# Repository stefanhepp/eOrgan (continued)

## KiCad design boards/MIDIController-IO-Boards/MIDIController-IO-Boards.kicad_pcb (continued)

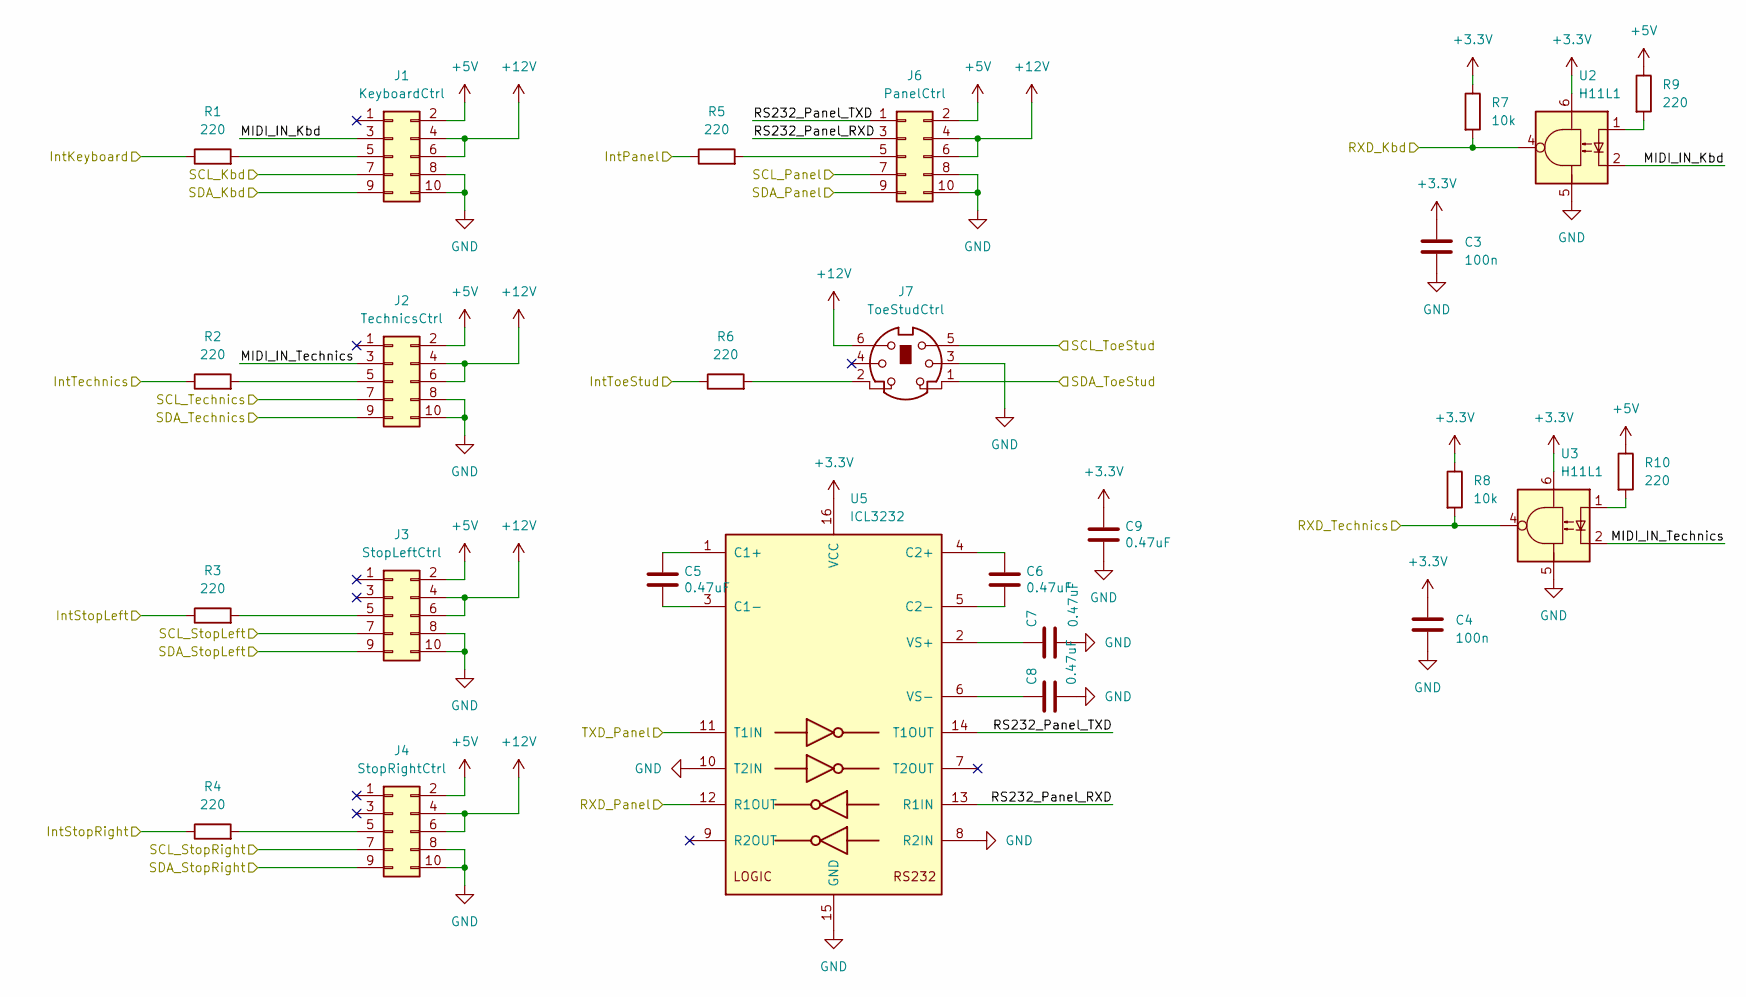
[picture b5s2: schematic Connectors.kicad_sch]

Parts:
C3, C4: 100n; C_Disc_D5.0mm_W2.5mm_P5.00mm
C5, C6, C7, C8, C9: 0.47uF; C_Rect_L7.0mm_W3.5mm_P5.00mm; Voltage 50V
J1: KeyboardCtrl; IDC-Header_2x05_P2.54mm_Horizontal
J2: TechnicsCtrl; IDC-Header_2x05_P2.54mm_Horizontal
J3: StopLeftCtrl; IDC-Header_2x05_P2.54mm_Horizontal
J4: StopRightCtrl; IDC-Header_2x05_P2.54mm_Horizontal
J6: PanelCtrl; IDC-Header_2x05_P2.54mm_Horizontal
J7: ToeStudCtrl; MiniDIN TE_5749180-1
R1, R2, R3, R4, R5, R6, R9, R10: 220; R_Axial_DIN0207_L6.3mm_D2.5mm_P10.16mm_Horizontal
R7, R8: 10k; R_Axial_DIN0207_L6.3mm_D2.5mm_P10.16mm_Horizontal
U2, U3: H11L1; DIP-6_W7.62mm
U5: ICL3232; DIP-16_W7.62mm

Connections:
+3.3V: C3.1, C4.1, C9.1, R7.1, R8.1, U2.6, U3.6, U5.16 (VCC); also elsewhere on the board
+5V: J1.2, J2.2, J3.2, J4.2, J6.2, R9.1, R10.1; also elsewhere on the board
+12V: J1.4, J1.6, J2.4, J2.6, J3.4, J3.6, J4.4, J4.6, J6.4, J6.6, J7.6; also elsewhere on the board
/Connectors/MIDI_IN_Kbd: J1.3, U2.2
/Connectors/MIDI_IN_Technics: J2.3, U3.2
/Connectors/RS232_Panel_RXD: J6.3, U5.13 (R1IN)
/Connectors/RS232_Panel_TXD: J6.1, U5.14 (T1OUT)
/IntKeyboard: R1.1; also elsewhere on the board
/IntPanel: R5.1; also elsewhere on the board
/IntStopLeft: R3.1; also elsewhere on the board
/IntStopRight: R4.1; also elsewhere on the board
/IntTechnics: R2.1; also elsewhere on the board
/IntToeStud: R6.1; also elsewhere on the board
/RXD_Kbd: R7.2, U2.4; also elsewhere on the board
/RXD_Panel: U5.12 (R1OUT); also elsewhere on the board
/RXD_Technics: R8.2, U3.4; also elsewhere on the board
/SCL_Kbd: J1.7; also elsewhere on the board
/SCL_Panel: J6.7; also elsewhere on the board
/SCL_StopLeft: J3.7; also elsewhere on the board
/SCL_StopRight: J4.7; also elsewhere on the board
/SCL_Technics: J2.7; also elsewhere on the board
/SCL_ToeStud: J7.5; also elsewhere on the board
/SDA_Kbd: J1.9; also elsewhere on the board
/SDA_Panel: J6.9; also elsewhere on the board
/SDA_StopLeft: J3.9; also elsewhere on the board
/SDA_StopRight: J4.9; also elsewhere on the board
/SDA_Technics: J2.9; also elsewhere on the board
/SDA_ToeStud: J7.1; also elsewhere on the board
/TXD_Panel: U5.11 (T1IN); also elsewhere on the board
GND: C3.2, C4.2, C7.2, C8.2, C9.2, J1.8, J1.10, J2.8, J2.10, J3.8, J3.10, J4.8, J4.10, J6.8, J6.10, J7.3, U2.5, U3.5, U5.8 (R2IN), U5.10 (T2IN), U5.15 (GND); also elsewhere on the board
unnamed: J1.5, R1.2
unnamed: J2.5, R2.2
unnamed: J3.5, R3.2
unnamed: J4.5, R4.2
unnamed: J6.5, R5.2
unnamed: J7.2, R6.2
unnamed: R9.2, U2.1
unnamed: R10.2, U3.1
unnamed: C5.1, U5.1 (C1+)
unnamed: C5.2, U5.3 (C1-)
unnamed: C6.1, U5.4 (C2+)
unnamed: C6.2, U5.5 (C2-)
unnamed: C7.1, U5.2 (VS+)
unnamed: C8.1, U5.6 (VS-)

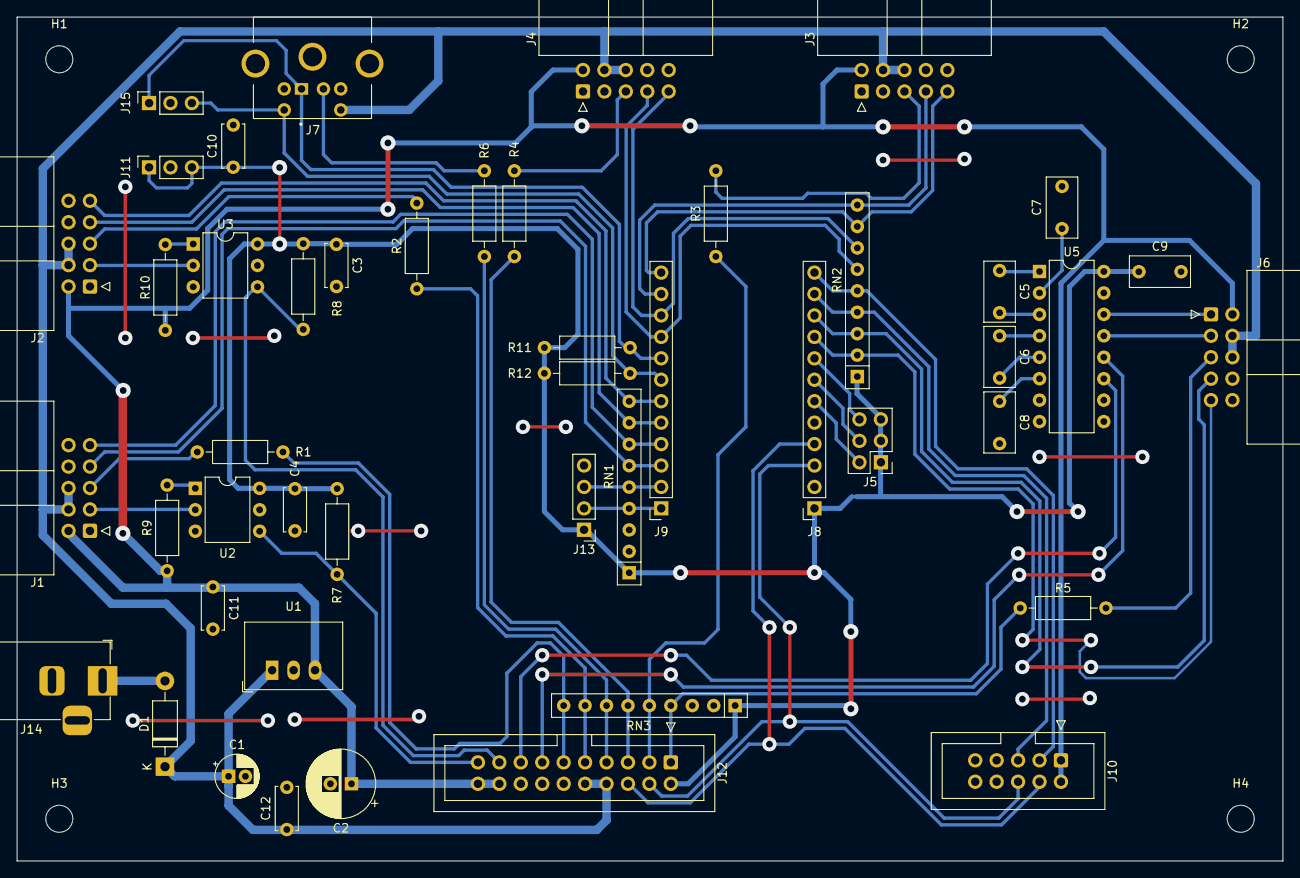
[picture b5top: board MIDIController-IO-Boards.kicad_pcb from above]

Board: 2 copper layers, 150.0 x 100.0 mm, 51 parts (0 on the bottom side), 54 nets.

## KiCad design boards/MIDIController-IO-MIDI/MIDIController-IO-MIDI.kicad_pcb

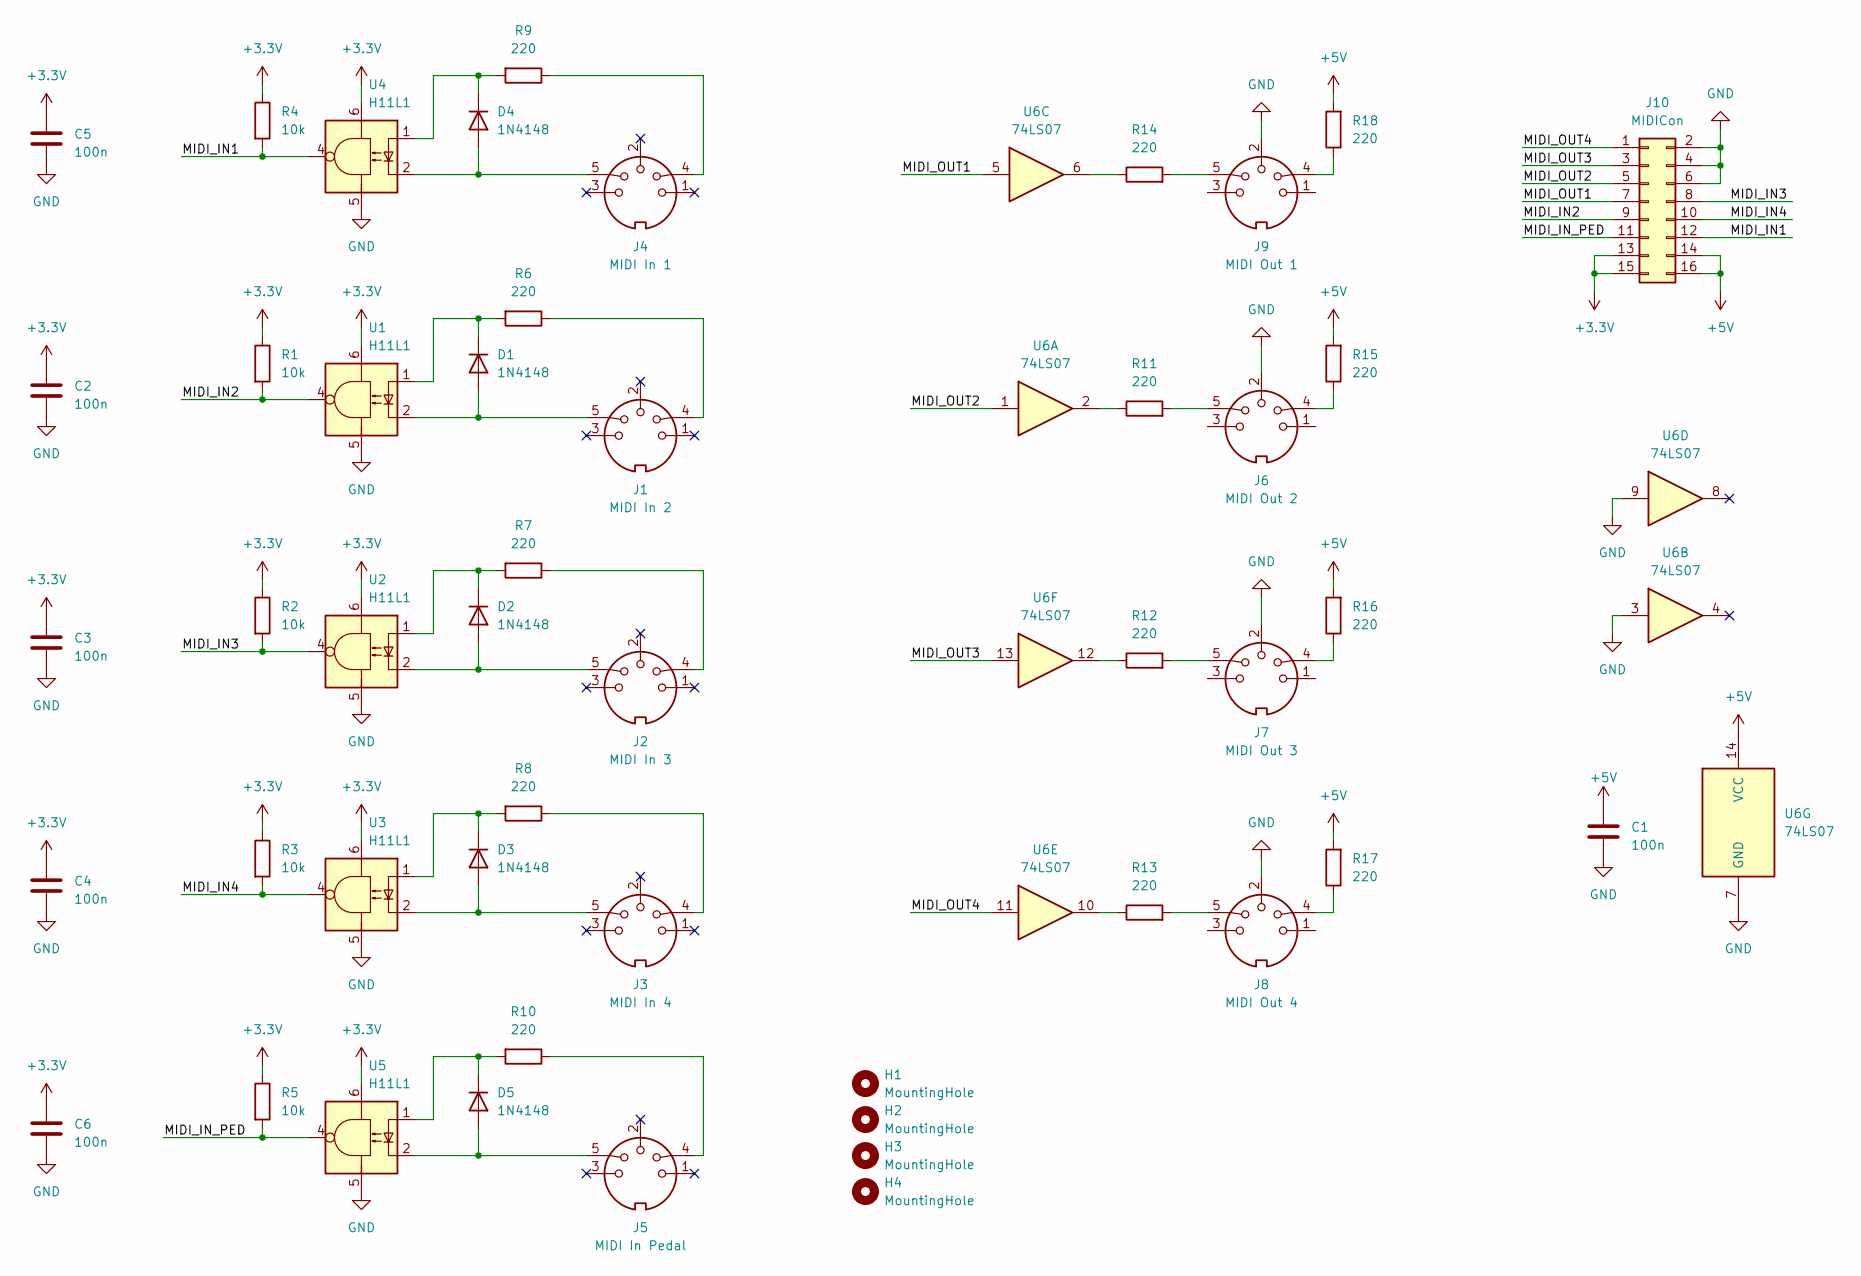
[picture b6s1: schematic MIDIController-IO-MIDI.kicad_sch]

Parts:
C1, C2, C3, C4, C5, C6: 100n; C_Disc_D5.0mm_W2.5mm_P5.00mm
D1, D2, D3, D4, D5: 1N4148; D_DO-35_SOD27_P7.62mm_Horizontal
H1, H2, H3, H4: MountingHole; MountingHole_3.2mm_M3
J1: MIDI In 2; DIN-5 MAB5P
J2: MIDI In 3; DIN-5 MAB5P
J3: MIDI In 4; DIN-5 MAB5P
J4: MIDI In 1; DIN-5 MAB5P
J5: MIDI In Pedal; DIN-5 MAB5P
J6: MIDI Out 2; DIN-5 MAB5P
J7: MIDI Out 3; DIN-5 MAB5P
J8: MIDI Out 4; DIN-5 MAB5P
J9: MIDI Out 1; DIN-5 MAB5P
J10: MIDICon; IDC-Header_2x08_P2.54mm_Vertical
R1, R2, R3, R4, R5: 10k; R_Axial_DIN0207_L6.3mm_D2.5mm_P10.16mm_Horizontal
R6, R7, R8, R9, R10, R11, R12, R13, R14, R15, R16, R17, R18: 220; R_Axial_DIN0207_L6.3mm_D2.5mm_P10.16mm_Horizontal
U1, U2, U3, U4, U5: H11L1; DIP-6_W7.62mm
U6: 74LS07; DIP-14_W7.62mm

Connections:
+3.3V: C2.1, C3.1, C4.1, C5.1, C6.1, J10.13, J10.15, R1.1, R2.1, R3.1, R4.1, R5.1, U1.6, U2.6, U3.6, U4.6, U5.6
+5V: C1.1, J10.14, J10.16, R15.2, R16.2, R17.2, R18.2, U6.14 (VCC)
/MIDI_IN1: J10.12, R4.2, U4.4
/MIDI_IN2: J10.9, R1.2, U1.4
/MIDI_IN3: J10.8, R2.2, U2.4
/MIDI_IN4: J10.10, R3.2, U3.4
/MIDI_IN_PED: J10.11, R5.2, U5.4
/MIDI_OUT1: J10.7, U6.5
/MIDI_OUT2: J10.5, U6.1
/MIDI_OUT3: J10.3, U6.13
/MIDI_OUT4: J10.1, U6.11
GND: C1.2, C2.2, C3.2, C4.2, C5.2, C6.2, J6.2, J7.2, J8.2, J9.2, J10.2, J10.4, J10.6, U1.5, U2.5, U3.5, U4.5, U5.5, U6.3, U6.7 (GND), U6.9
unnamed: D1.2 (A), J1.5, U1.2
unnamed: D1.1 (K), R6.2, U1.1
unnamed: D2.2 (A), J2.5, U2.2
unnamed: D2.1 (K), R7.2, U2.1
unnamed: D3.2 (A), J3.5, U3.2
unnamed: D3.1 (K), R8.2, U3.1
unnamed: D4.2 (A), J4.5, U4.2
unnamed: D4.1 (K), R9.2, U4.1
unnamed: D5.2 (A), J5.5, U5.2
unnamed: D5.1 (K), R10.2, U5.1
unnamed: J1.4, R6.1
unnamed: J2.4, R7.1
unnamed: J3.4, R8.1
unnamed: J4.4, R9.1
unnamed: J5.4, R10.1
unnamed: J6.4, R15.1
unnamed: J6.5, R11.2
unnamed: J7.4, R16.1
unnamed: J7.5, R12.2
unnamed: J8.4, R17.1
unnamed: J8.5, R13.2
unnamed: J9.4, R18.1
unnamed: J9.5, R14.2
unnamed: R11.1, U6.2
unnamed: R12.1, U6.12
unnamed: R13.1, U6.10
unnamed: R14.1, U6.6

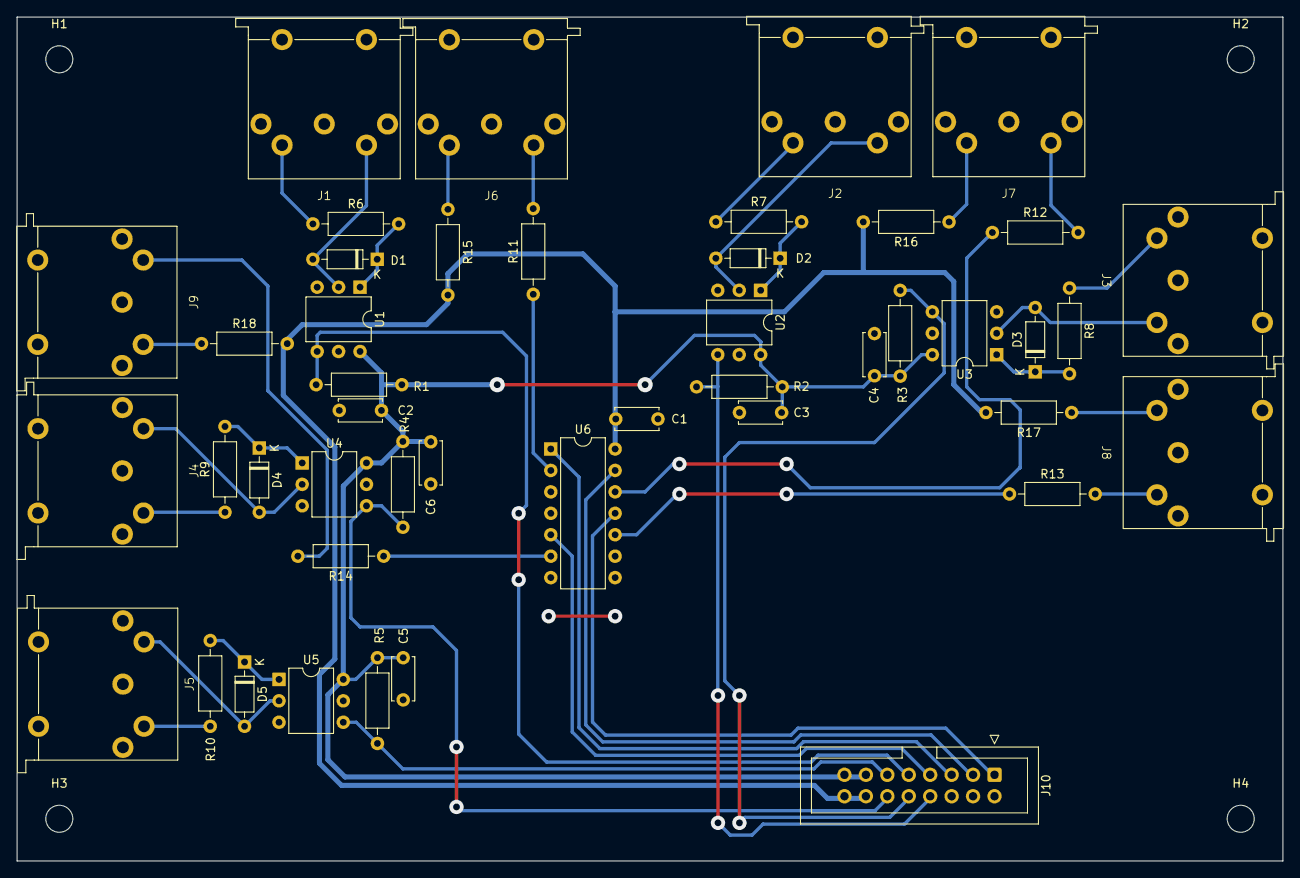
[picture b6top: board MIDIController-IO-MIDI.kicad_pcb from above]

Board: 2 copper layers, 150.0 x 100.0 mm, 49 parts (0 on the bottom side), 39 nets.

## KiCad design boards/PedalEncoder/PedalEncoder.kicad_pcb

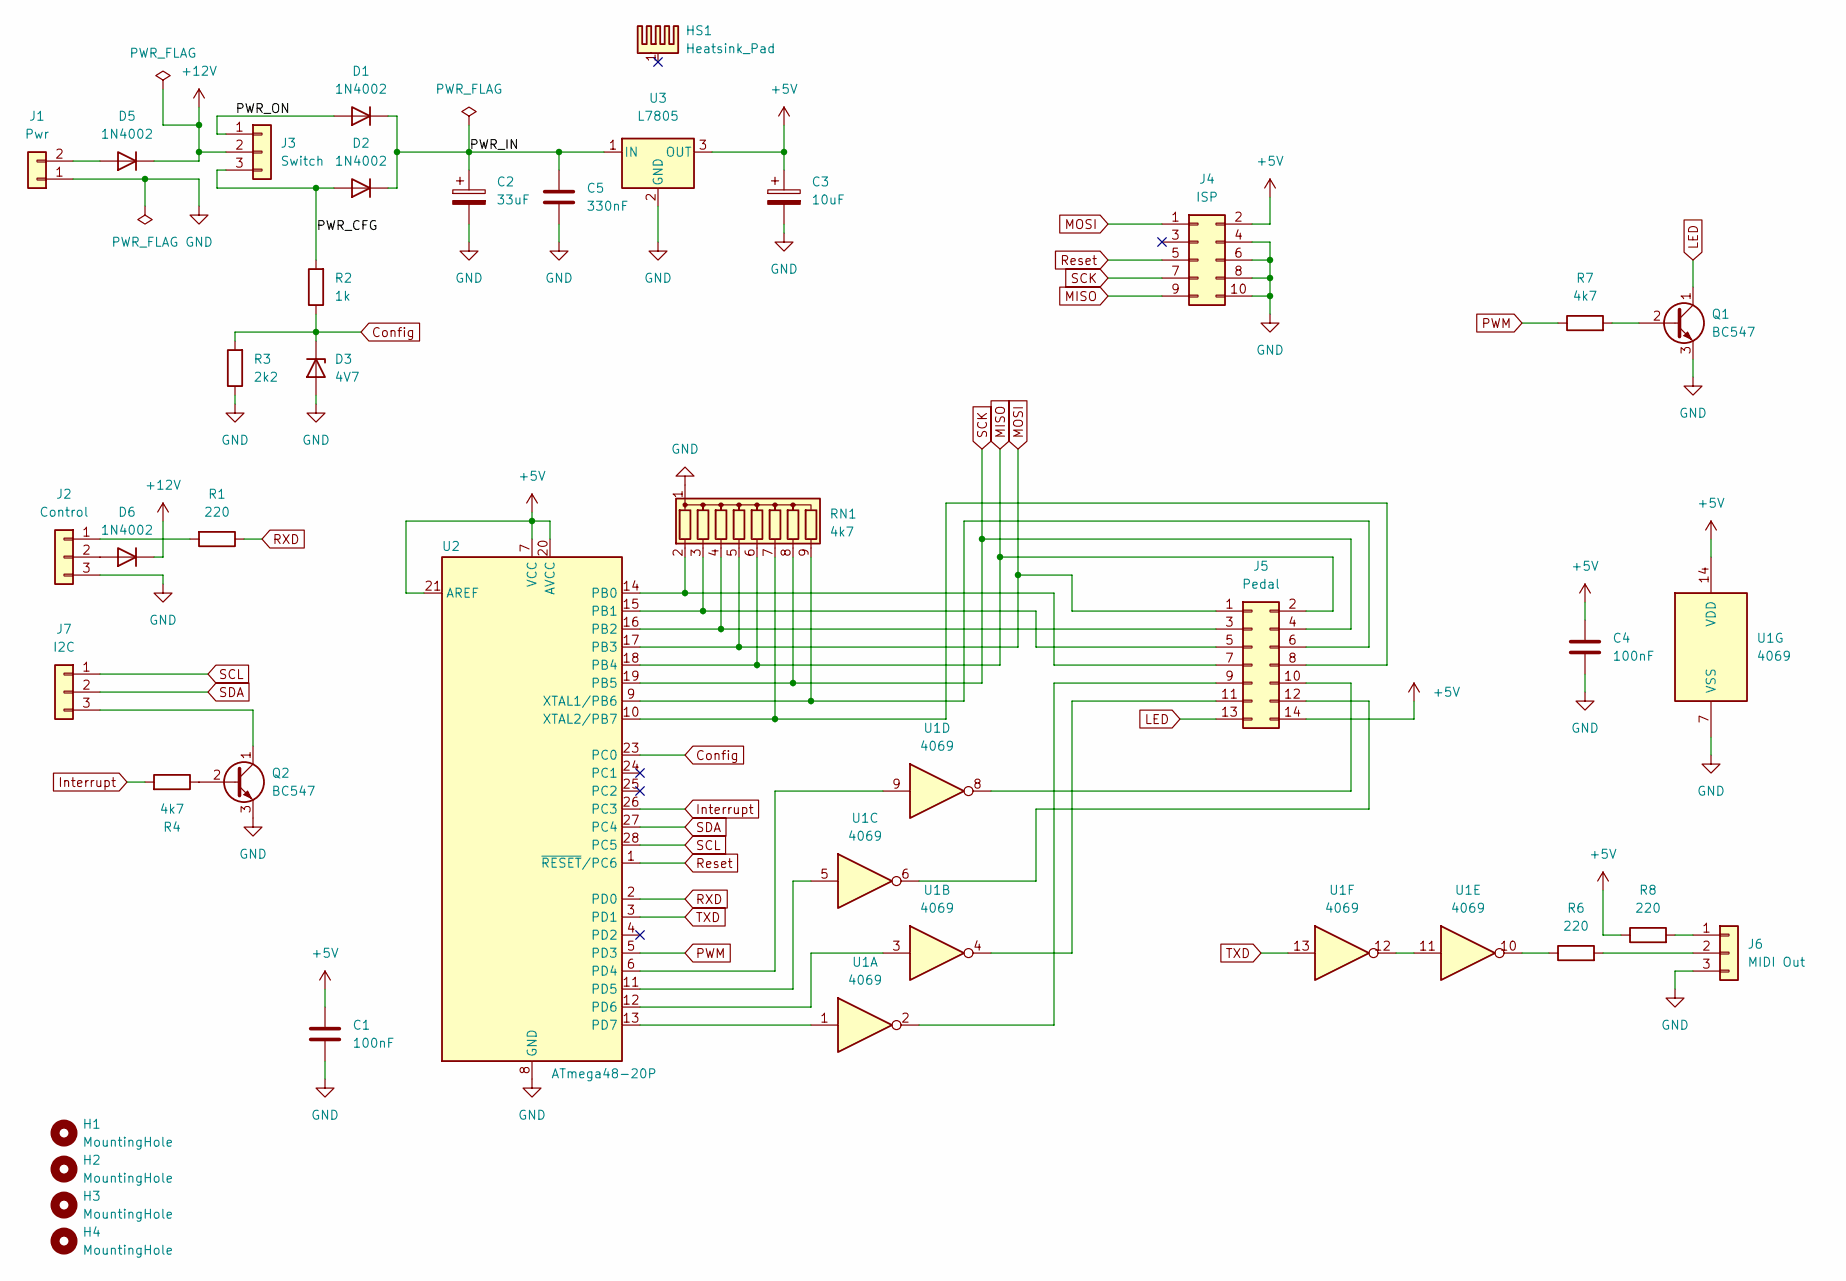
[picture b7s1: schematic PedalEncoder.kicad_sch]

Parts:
C1, C4: 100nF; C_Disc_D7.5mm_W2.5mm_P5.00mm
C2: 33uF; CP_Radial_D8.0mm_P2.50mm
C3: 10uF; CP_Radial_D8.0mm_P2.50mm
C5: 330nF; C_Disc_D7.5mm_W2.5mm_P5.00mm
D1, D2: 1N4002; D_DO-41_SOD81_P3.81mm_Vertical_AnodeUp
D3: 4V7; D_DO-15_P3.81mm_Vertical_AnodeUp
D5, D6: 1N4002; D_DO-41_SOD81_P7.62mm_Horizontal
H1, H2, H3, H4: MountingHole; MountingHole_3mm
HS1: Heatsink_Pad; Heatsink_Aavid_TO-220_H12.7mm
J1: Pwr; PinHeader_1x02_P2.54mm_Vertical
J2: Control; PinHeader_1x03_P2.54mm_Vertical
J3: Switch; PinHeader_1x03_P2.54mm_Vertical
J4: ISP; IDC-Header_2x05_P2.54mm_Vertical
J5: Pedal; PinHeader_2x07_P2.54mm_Vertical
J6: MIDI Out; PinHeader_1x03_P2.54mm_Vertical
J7: I2C; PinHeader_1x03_P2.54mm_Vertical
Q1, Q2: BC547; TO-92L_Inline
R1: 220; R_Axial_DIN0207_L6.3mm_D2.5mm_P10.16mm_Horizontal
R2: 1k; R_Axial_DIN0207_L6.3mm_D2.5mm_P2.54mm_Vertical
R3: 2k2; R_Axial_DIN0207_L6.3mm_D2.5mm_P2.54mm_Vertical
R4: 4k7; R_Axial_DIN0207_L6.3mm_D2.5mm_P2.54mm_Vertical
R6, R8: 220; R_Axial_DIN0207_L6.3mm_D2.5mm_P2.54mm_Vertical
R7: 4k7; R_Axial_DIN0207_L6.3mm_D2.5mm_P10.16mm_Horizontal
RN1: 4k7; R_Array_SIP9
U1: 4069; DIP-14_W7.62mm
U2: ATmega48-20P; DIP-28_W7.62mm_Socket
U3: L7805; TO-220-3_Vertical

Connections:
+5V: C1.1, C3.1, C4.1, J4.2, J5.14, R8.1, U1.14 (VDD), U2.7 (VCC), U2.20 (AVCC), U2.21 (AREF), U3.3 (OUT)
+12V: D5.1 (K), D6.1 (K), J3.2
/PWR_CFG: D2.2 (A), J3.3, R2.2
/PWR_IN: C2.1, C5.1, D1.1 (K), D2.1 (K), U3.1 (IN)
/PWR_ON: D1.2 (A), J3.1
Config: D3.1 (K), R2.1, R3.2, U2.23 (PC0)
GND: C1.2, C2.2, C3.2, C4.2, C5.2, D3.2 (A), J1.1, J2.3, J4.4, J4.6, J4.8, J4.10, J6.3, Q1.3 (E), Q2.3 (E), R3.1, RN1.1 (common), U1.7 (VSS), U2.8 (GND), U2.22 (GND), U3.2 (GND)
Interrupt: R4.2, U2.26 (PC3)
LED: J5.13, Q1.1 (C)
MISO: J4.9, J5.2, RN1.6 (R5), U2.18 (PB4)
MOSI: J4.1, J5.1, RN1.5 (R4), U2.17 (PB3)
unnamed: D5.2 (A), J1.2
unnamed: D6.2 (A), J2.2
unnamed: J2.1, R1.2
unnamed: J5.3, RN1.4 (R3), U2.16 (PB2)
unnamed: J5.5, RN1.3 (R2), U2.15 (PB1)
unnamed: J5.6, RN1.9 (R8), U2.9 (XTAL1/PB6)
unnamed: J5.7, RN1.2 (R1), U2.14 (PB0)
unnamed: J5.8, RN1.7 (R6), U2.10 (XTAL2/PB7)
unnamed: J5.9, U1.2
unnamed: J5.10, U1.8
unnamed: J5.11, U1.4
unnamed: J5.12, U1.6
unnamed: J6.1, R8.2
unnamed: J6.2, R6.2
unnamed: J7.3, Q2.1 (C)
unnamed: Q1.2 (B), R7.2
unnamed: Q2.2 (B), R4.1
unnamed: R6.1, U1.10
unnamed: U1.11, U1.12
unnamed: U1.9, U2.6 (PD4)
unnamed: U1.5, U2.11 (PD5)
unnamed: U1.3, U2.12 (PD6)
unnamed: U1.1, U2.13 (PD7)
PWM: R7.1, U2.5 (PD3)
RXD: R1.1, U2.2 (PD0)
Reset: J4.5, U2.1 (~RESET/PC6)
SCK: J4.7, J5.4, RN1.8 (R7), U2.19 (PB5)
SCL: J7.1, U2.28 (PC5)
SDA: J7.2, U2.27 (PC4)
TXD: U1.13, U2.3 (PD1)

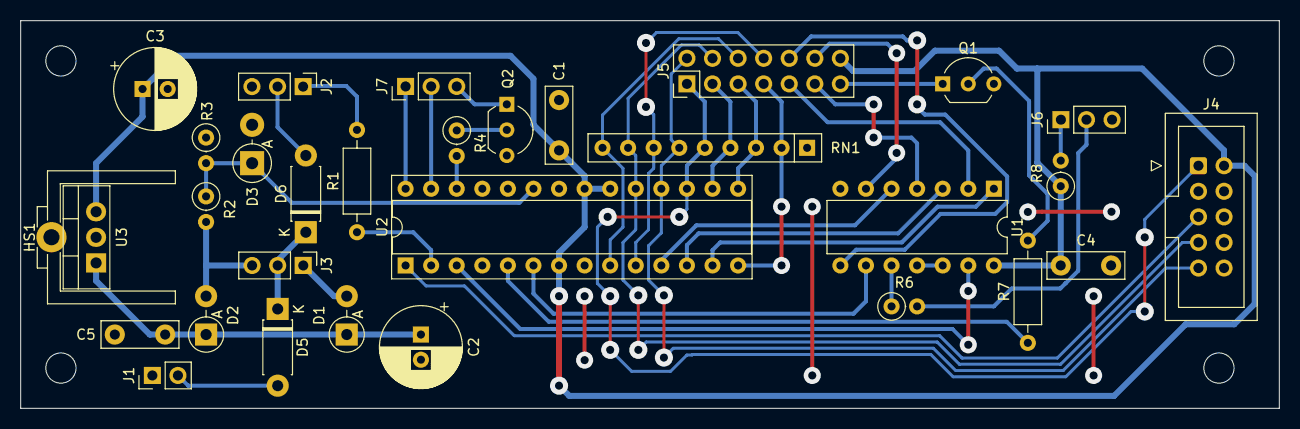
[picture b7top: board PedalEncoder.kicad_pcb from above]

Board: 2 copper layers, 125.0 x 38.5 mm, 35 parts (0 on the bottom side), 41 nets.
